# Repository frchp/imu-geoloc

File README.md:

# imu-geoloc
Goal is to have HW + embedded SW to keep track of position

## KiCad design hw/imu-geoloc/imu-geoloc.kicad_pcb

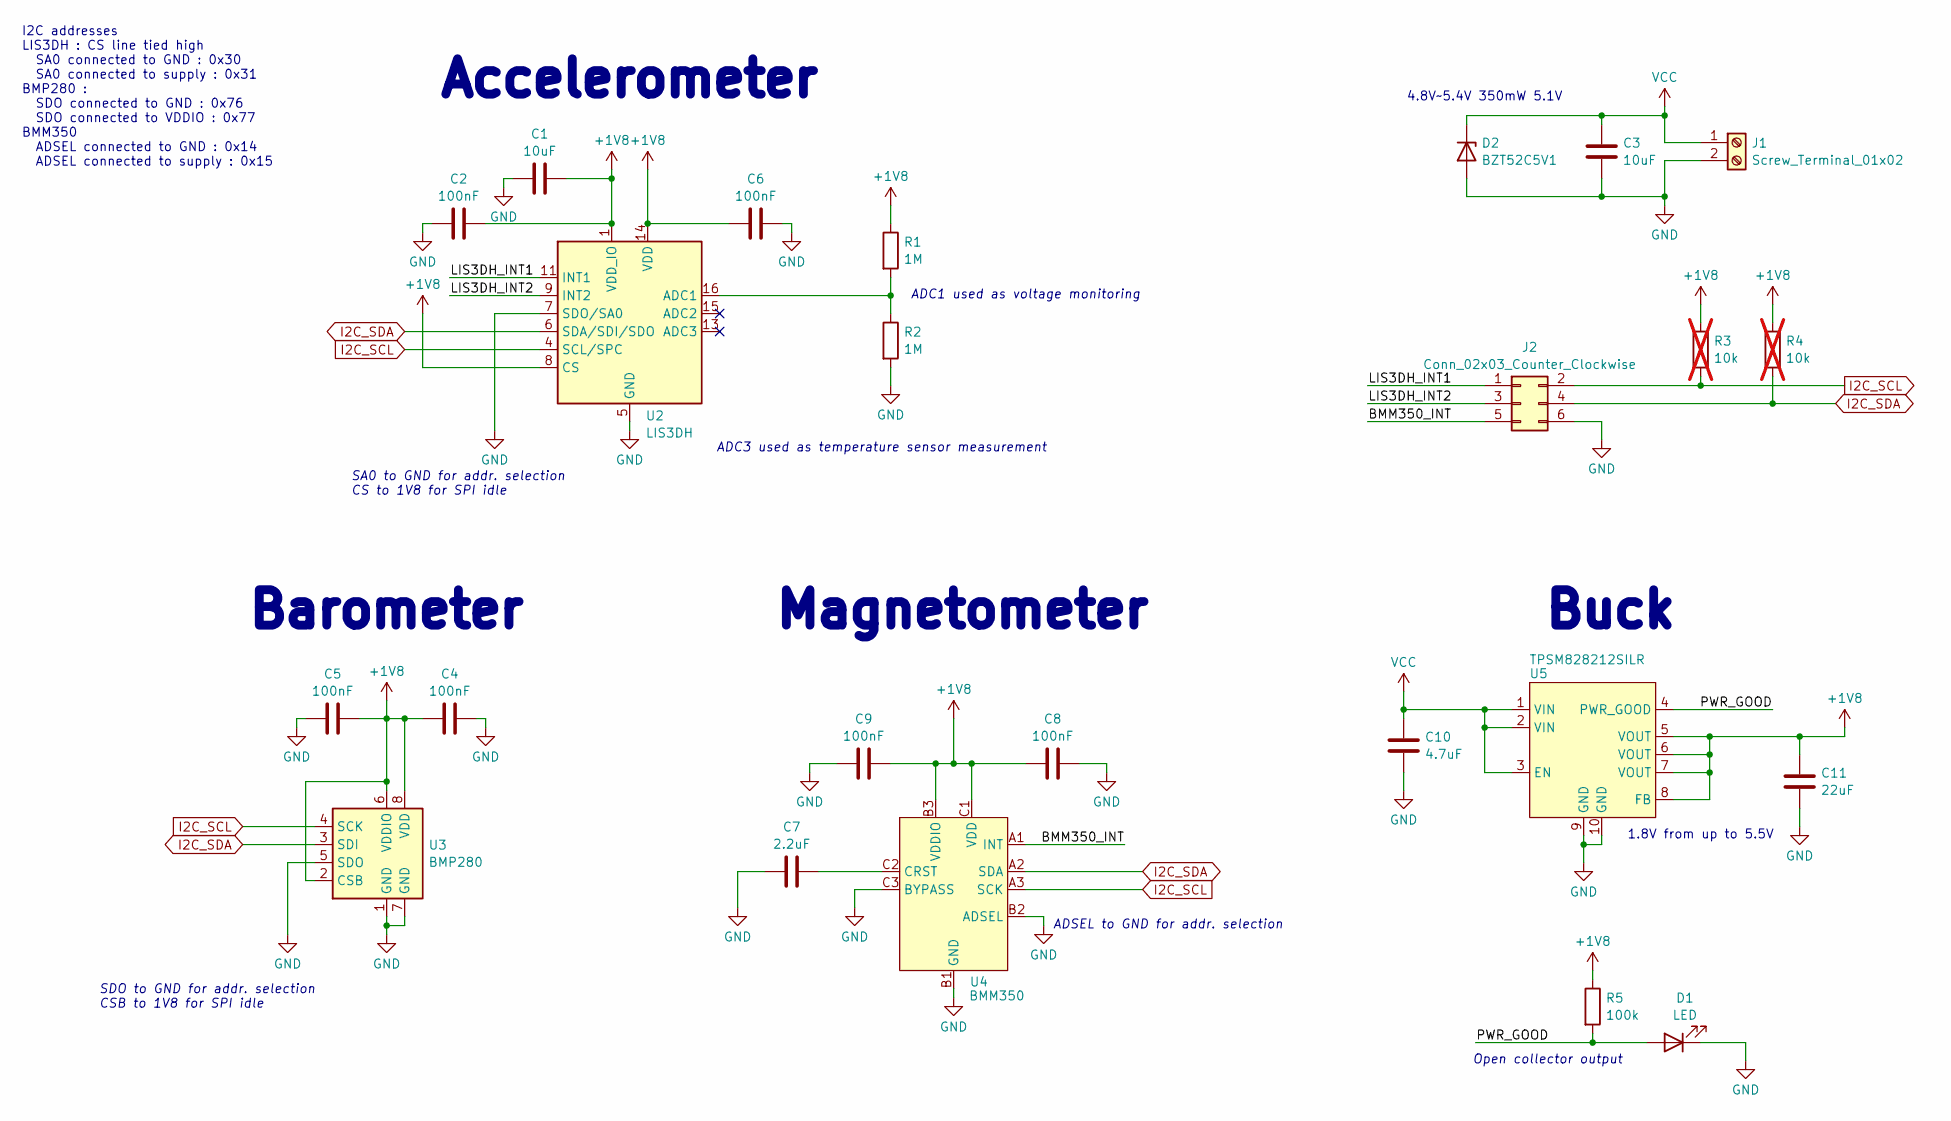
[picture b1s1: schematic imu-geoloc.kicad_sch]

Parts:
C1, C3: 10uF; C_0805_2012Metric
C2, C4, C5, C6, C8, C9: 100nF; C_0603_1608Metric
C7: 2.2uF; C_0805_2012Metric
C10: 4.7uF; C_0805_2012Metric
C11: 22uF; C_0805_2012Metric
D1: LED; LED_0603_1608Metric
D2: BZT52C5V1; D_SOD-123
J1: Screw_Terminal_01x02; TerminalBlock_bornier-2_P5.08mm
J2: Conn_02x03_Counter_Clockwise; PinHeader_2x03_P2.54mm_Vertical
R1, R2: 1M; R_0603_1608Metric
R3, R4: 10k; R_0603_1608Metric; not fitted
R5: 100k; R_0603_1608Metric
U2: LIS3DH; LGA-16_3x3mm_P0.5mm_LayoutBorder3x5y
U3: BMP280; Bosch_LGA-8_2x2.5mm_P0.65mm_ClockwisePinNumbering
U4: BMM350; WLCSP-9_1.21x1.22mm_P0.4mm
U5: TPSM828212SILR; uSIP10

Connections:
+1V8: C1.2, C2.2, C4.2, C5.2, C6.2, C8.1, C9.2, C11.1, R1.1, R3.1, R4.1, R5.1, U2.1 (VDD_IO), U2.8 (CS), U2.14 (VDD), U3.2 (CSB), U3.6 (VDDIO), U3.8 (VDD), U4.B3 (VDDIO), U4.C1 (VDD), U5.5 (VOUT), U5.6 (VOUT), U5.7 (VOUT), U5.8 (FB)
/BMM350_INT: J2.5, U4.A1 (INT)
/LIS3DH_INT1: J2.1, U2.11 (INT1)
/LIS3DH_INT2: J2.3, U2.9 (INT2)
/PWR_GOOD: D1.2 (A), R5.2, U5.4 (PWR_GOOD)
GND: C1.1, C2.1, C3.2, C4.1, C5.1, C6.1, C7.1, C8.2, C9.1, C10.2, C11.2, D1.1 (K), D2.2 (A), J1.2, J2.6, R2.2, U2.5 (GND), U2.7 (SDO/SA0), U2.10 (GND), U2.12 (GND), U3.1 (GND), U3.5 (SDO), U3.7 (GND), U4.B1 (GND), U4.B2 (ADSEL), U4.C3 (BYPASS), U5.9 (GND), U5.10 (GND)
I2C_SCL: J2.2, R3.2, U2.4 (SCL/SPC), U3.4 (SCK), U4.A3 (SCK)
I2C_SDA: J2.4, R4.2, U2.6 (SDA/SDI/SDO), U3.3 (SDI), U4.A2 (SDA)
unnamed: R1.2, R2.1, U2.16 (ADC1)
unnamed: C7.2, U4.C2 (CRST)
VCC: C3.1, C10.1, D2.1 (K), J1.1, U5.1 (VIN), U5.2 (VIN), U5.3 (EN)

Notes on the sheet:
SDO to GND for addr. selection CSB to 1V8 for SPI idle
1.8V from up to 5.5V
ADC1 used as voltage monitoring
I2C addresses LIS3DH : CS line tied high SA0 connected to GND : 0x30 SA0 connected to supply : 0x31 BMP280 : SDO connected to GND : 0x76 SDO connected to VDDIO : 0x77 BMM350 ADSEL connected to GND : 0x14 ADSEL connected to supply : 0x15
Magnetometer
Open collector output
ADC3 used as temperature sensor measurement
ADSEL to GND for addr. selection
Accelerometer
Buck
Barometer
4.8V~5.4V 350mW 5.1V
SA0 to GND for addr. selection CS to 1V8 for SPI idle

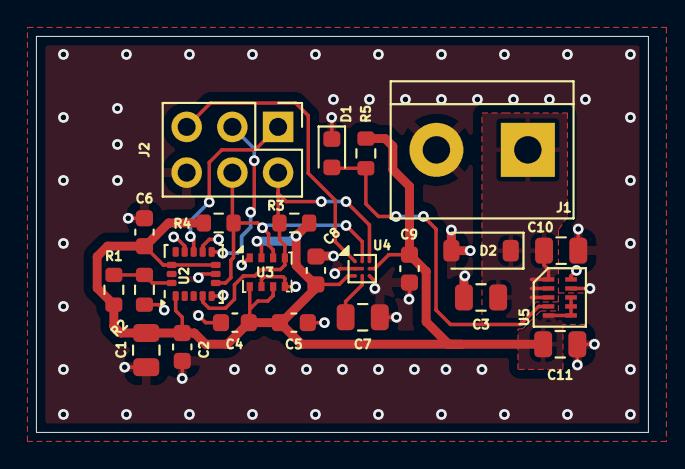
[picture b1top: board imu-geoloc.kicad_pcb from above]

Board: 2 copper layers, 34.0 x 22.0 mm, 24 parts (0 on the bottom side), 11 nets.

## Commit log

2025-02-22 Create Kicad project
2025-02-22 Add some doc
2025-02-22 HW version A00
